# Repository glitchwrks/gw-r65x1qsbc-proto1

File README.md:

R65X1Q Prototyping Board
========================

This project is a prototyping board for the [Glitch Works R65X1Q Single Board Computer](https://www.tindie.com/products/21523/). It provides a pad-per-hole board with dedicated areas for the Glitchbus, `PORT B`, and `PORT D` connectors on the SBC. All signal pins are labeled on front and back.

Aside from being a useful prototyping board, this project can be used as the starting point for a custom expansion PCB for the R65X1Q SBC.

Note that if you're not using the `PORT B` and/or `PORT D` features of the SBC, you're likely better off using a standard Glitchbus prototyping board, since other computers will be compatible with it.

License
-------

This project is released under the GNU GPLv3, a copy of which should be included with the project files.

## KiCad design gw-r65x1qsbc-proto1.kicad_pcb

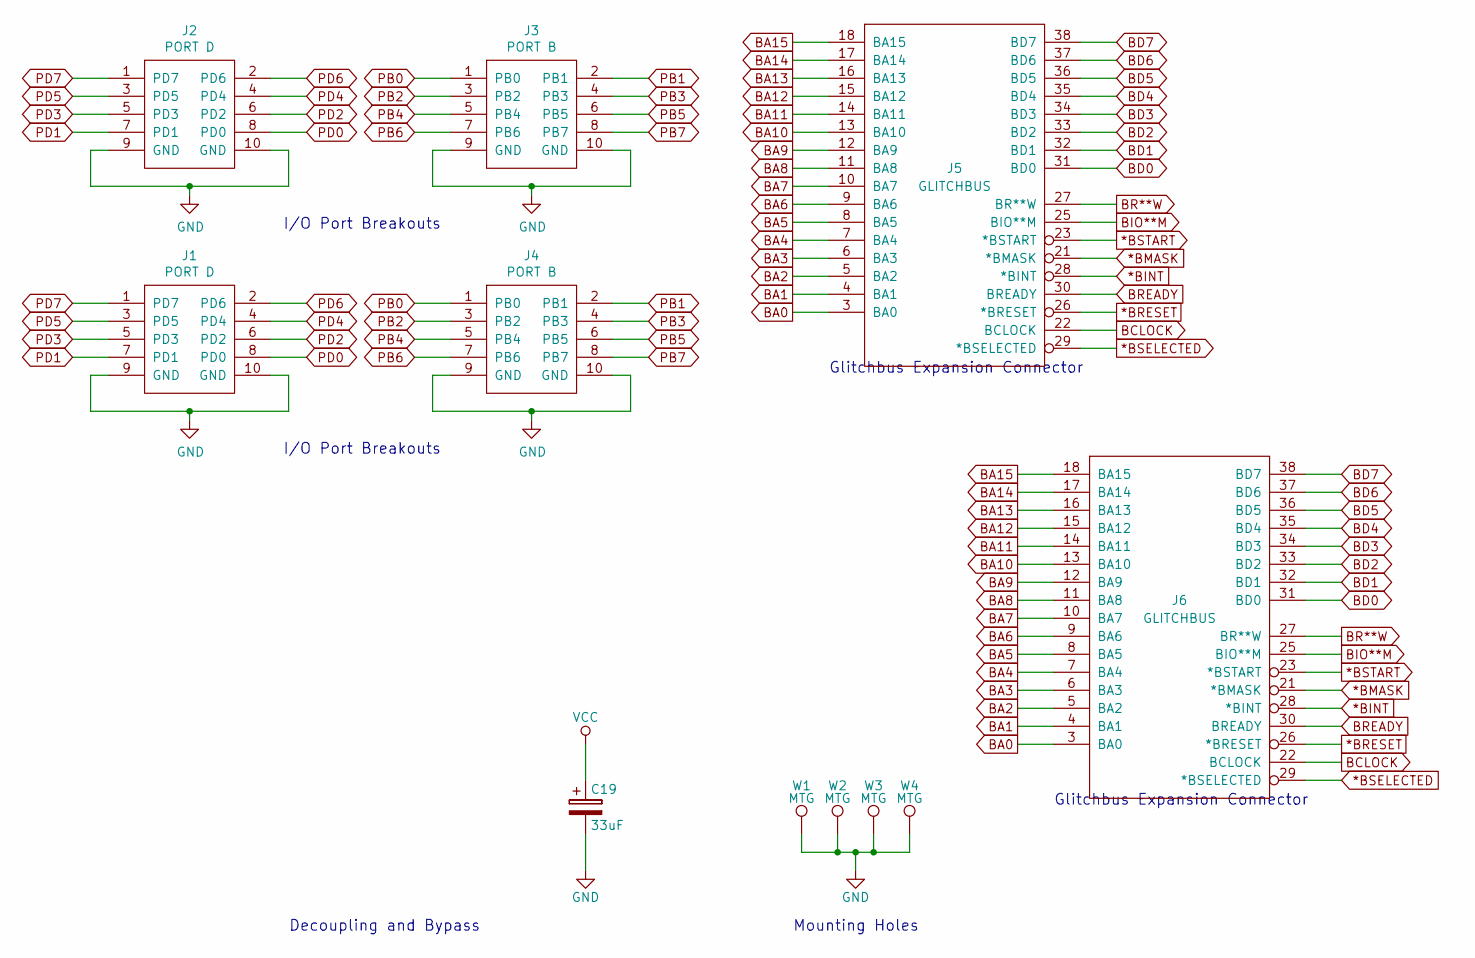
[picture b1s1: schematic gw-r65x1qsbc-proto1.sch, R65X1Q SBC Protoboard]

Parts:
C19: 33uF; CP_AX_700_200
J1: PORT D; STRAIGHT_2x5_NOSILK
J2: PORT D; STRAIGHT_2x5
J3: PORT B; STRAIGHT_2x5_NOSILK
J4: PORT B; STRAIGHT_2x5
J5: GLITCHBUS; STRAIGHT_2x20_NOSILK
J6: GLITCHBUS; STRAIGHT_2x20
W1, W2, W3, W4: MTG; 120mil_no_silkscreen

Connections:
*BINT: J5.28 (*BINT), J6.28 (*BINT)
*BMASK: J5.21 (*BMASK), J6.21 (*BMASK)
*BRESET: J5.26 (*BRESET), J6.26 (*BRESET)
*BSELECTED: J5.29 (*BSELECTED), J6.29 (*BSELECTED)
*BSTART: J5.23 (*BSTART), J6.23 (*BSTART)
BA0: J5.3 (BA0), J6.3 (BA0)
BA1: J5.4 (BA1), J6.4 (BA1)
BA2: J5.5 (BA2), J6.5 (BA2)
BA3: J5.6 (BA3), J6.6 (BA3)
BA4: J5.7 (BA4), J6.7 (BA4)
BA5: J5.8 (BA5), J6.8 (BA5)
BA6: J5.9 (BA6), J6.9 (BA6)
BA7: J5.10 (BA7), J6.10 (BA7)
BA8: J5.11 (BA8), J6.11 (BA8)
BA9: J5.12 (BA9), J6.12 (BA9)
BA10: J5.13 (BA10), J6.13 (BA10)
BA11: J5.14 (BA11), J6.14 (BA11)
BA12: J5.15 (BA12), J6.15 (BA12)
BA13: J5.16 (BA13), J6.16 (BA13)
BA14: J5.17 (BA14), J6.17 (BA14)
BA15: J5.18 (BA15), J6.18 (BA15)
BCLOCK: J5.22 (BCLOCK), J6.22 (BCLOCK)
BD0: J5.31 (BD0), J6.31 (BD0)
BD1: J5.32 (BD1), J6.32 (BD1)
BD2: J5.33 (BD2), J6.33 (BD2)
BD3: J5.34 (BD3), J6.34 (BD3)
BD4: J5.35 (BD4), J6.35 (BD4)
BD5: J5.36 (BD5), J6.36 (BD5)
BD6: J5.37 (BD6), J6.37 (BD6)
BD7: J5.38 (BD7), J6.38 (BD7)
BIO**M: J5.25 (BIO**M), J6.25 (BIO**M)
BR**W: J5.27 (BR**W), J6.27 (BR**W)
BREADY: J5.30 (BREADY), J6.30 (BREADY)
GND: C19.2, J1.9 (GND), J1.10 (GND), J2.9 (GND), J2.10 (GND), J3.9 (GND), J3.10 (GND), J4.9 (GND), J4.10 (GND), J5.19 (GND), J5.20 (GND), J5.24 (GND), J5.39 (GND), J5.40 (GND), J6.19 (GND), J6.20 (GND), J6.24 (GND), J6.39 (GND), J6.40 (GND), W1.1, W2.1, W3.1, W4.1
PB0: J3.1 (PB0), J4.1 (PB0)
PB1: J3.2 (PB1), J4.2 (PB1)
PB2: J3.3 (PB2), J4.3 (PB2)
PB3: J3.4 (PB3), J4.4 (PB3)
PB4: J3.5 (PB4), J4.5 (PB4)
PB5: J3.6 (PB5), J4.6 (PB5)
PB6: J3.7 (PB6), J4.7 (PB6)
PB7: J3.8 (PB7), J4.8 (PB7)
PD0: J1.8 (PD0), J2.8 (PD0)
PD1: J1.7 (PD1), J2.7 (PD1)
PD2: J1.6 (PD2), J2.6 (PD2)
PD3: J1.5 (PD3), J2.5 (PD3)
PD4: J1.4 (PD4), J2.4 (PD4)
PD5: J1.3 (PD5), J2.3 (PD5)
PD6: J1.2 (PD6), J2.2 (PD6)
PD7: J1.1 (PD7), J2.1 (PD7)
VCC: C19.1, J5.1 (VCC), J5.2 (VCC), J6.1 (VCC), J6.2 (VCC)

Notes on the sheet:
Glitchbus Expansion Connector
Mounting Holes
Decoupling and Bypass
I/O Port Breakouts

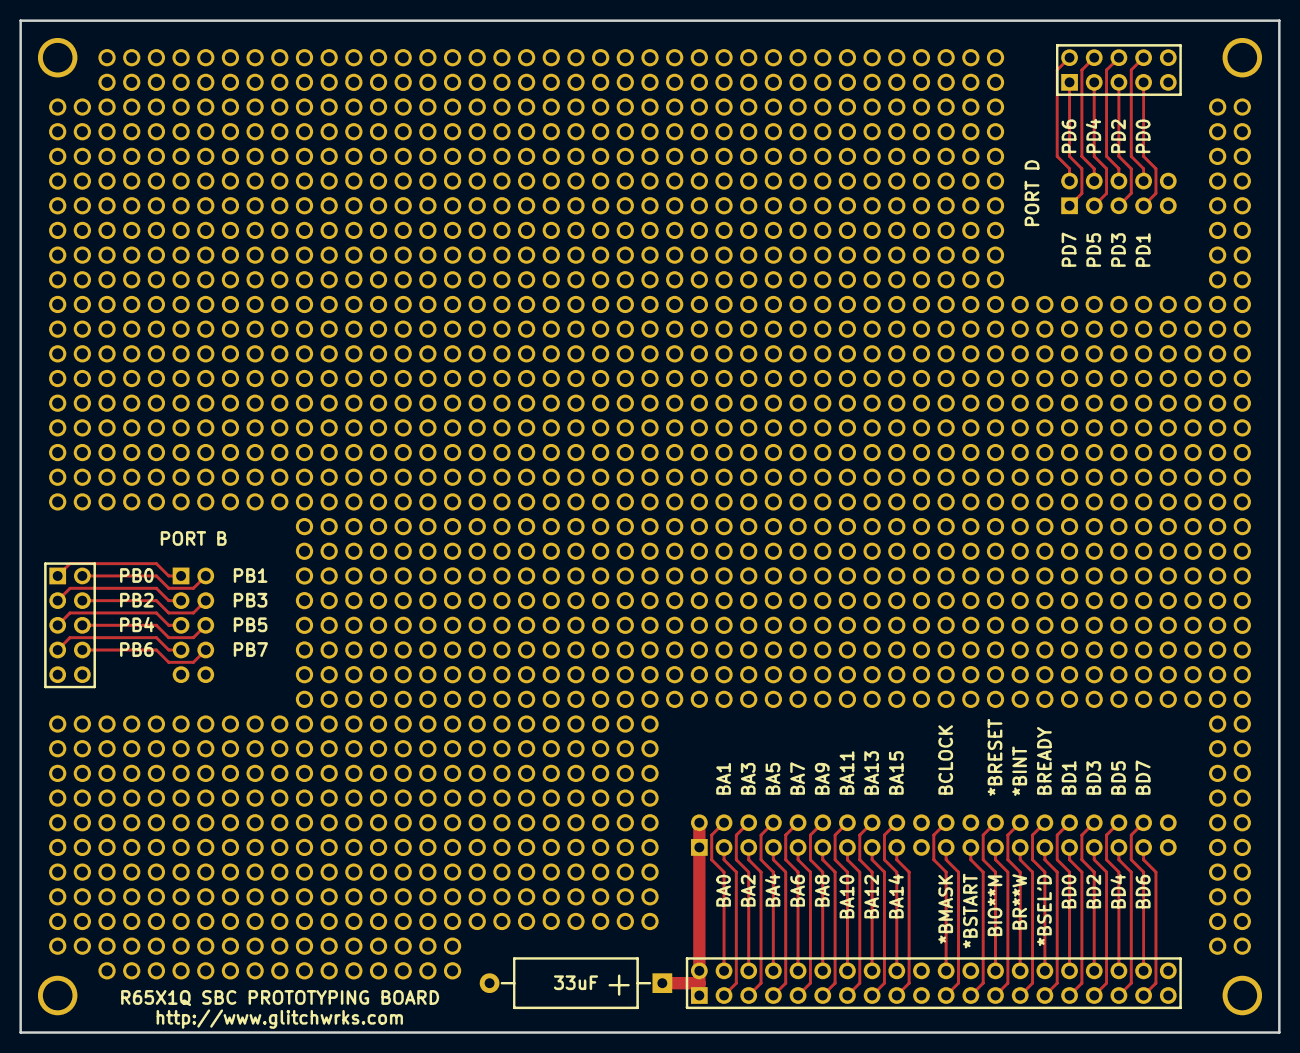
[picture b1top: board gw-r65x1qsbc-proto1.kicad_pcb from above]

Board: 2 copper layers, 129.5 x 104.1 mm, 11 parts (0 on the bottom side), 51 nets.

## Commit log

2023-12-14 WIP bringing in board outline, Glitchbus and PORT B, D positions
2023-12-14 PROTOTYPE 1
2023-12-14 Changing to solid thermal connection for mounting holes
2023-12-14 Adding README, licensing info
